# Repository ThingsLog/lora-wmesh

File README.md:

# W-Mesh — reference implementation (Stage 1)

W-Mesh exists to solve one concrete problem: **covering Livingston Island
(Antarctica) with a sensor network without deploying gateway infrastructure
across it**. The Bulgarian Antarctic base runs a duty-cycled LoRaWAN network
— everything sleeps except a ~15-minute daily window — but LoRaWAN is
single-hop, and every additional gateway site (battery, solar, mast) is
infrastructure that must survive the polar winter unattended. Many target
sites (glaciers, ridges, neighbouring bays) can be visited only briefly,
some only by drone.

W-Mesh extends the same windowed, buffered telemetry system with multi-hop
store-and-forward instead: battery relays on ridge lines carry the traffic
of whole valleys and glaciers back to the single existing gateway. Cascade
phases ordered by hop depth, loop freedom by a gradient rule, CAD-gated
listening, and years of battery life on primary cells — coverage grows,
infrastructure does not.

> The underlying windowed deployment this builds on is described in:
> N. Milovanov, B. Tzankov and P. Sapundzhiev, *"Deployment of a low-power
> LoRa LPWAN sensor network for environmental monitoring in Antarctica,"*
> Proc. CompSysTech '26 (Best Paper Award).

Livingston Island is the first deployment, not the limit. The protocol can
be used in **any LoRa/LoRaWAN network whose reach has to grow but where
extra gateways cannot be added, or are not practical to add** — assets one
ridge beyond the last covered valley in water-utility telemetry, remote
farmland, mountain instrumentation, island chains. The mesh layer is
payload-agnostic (relays forward the LoRaWAN frame byte-for-byte and never
read it), so it carries any application format; a device only has to adopt
the windowed discipline: buffer, one slot per day, a fixed channel, the
CAD-length preamble.

## The protocol in short

**The premise.** The whole network — gateway, satellite backhaul, every
node — is asleep except for one scheduled window per day (Livingston:
~15 minutes, anchored at the gateway's Class B beacon around 12:05 UTC).
Nodes buffer a full day of readings and deliver them in that window.
LoRaWAN alone is single-hop; W-Mesh adds store-and-forward on top of it
without touching the LoRaWAN frame.

**The cascade.** The window opens with a short beacon **pre-roll**: the
gateway emits the standard Class B beacon, and relays re-broadcast it
outward tier by tier (in per-relay sub-slots), so every node re-anchors
its clock for the day. Then the uplink **phases** run in order of
DECREASING depth: the deepest tier transmits first while its parents
listen (CAD-gated, ~700× cheaper than continuous RX); each relay then
transmits its own data plus everything it stored, one tier closer to the
gateway per phase. Within a phase every node owns a provisioned time
slot; within the island every tier-1 subtree owns one fixed channel.
Loop freedom needs no timers: a node forwards only frames arriving from
STRICTLY GREATER depth (the gradient rule), so the forwarding graph is a
DAG by construction. One window, one sequence:

**The nodes.** One binary, three provisioned profiles:

| Profile | Measures | Listens | GNSS | Radio budget |
|---|---|---|---|---|
| **leaf** | environment (T/RH) + battery | beacon only | none | ~0.03 mAh/day |
| **relay** | same + forwards its subtree | beacon + CAD phase | optional backup clock (`gnssbk`) | up to ~0.6 mAh/day |
| **stake** | its own GNSS position + battery | beacon only | yes — position IS the payload | ~5 mAh/day (GNSS dominated) |

A stake is technically a leaf (no children); it is a separate profile only
because its payload is the daily averaged GNSS position — the glacier
application. Every profile carries the battery (mV) as its last port.

**The mesh header — where it goes in and where it comes out.** Three
bytes — origin id, sequence, depth|TTL — **prepended to, never written
into, the LoRaWAN frame**:

- **Inserted** by the originating node at transmission; **rewritten** by
  every relay on forward (own depth stamped, TTL decremented). The
  LoRaWAN PHYPayload behind it — ciphertext, frame counter, MIC — is
  forwarded byte-for-byte: relays hold no session keys and need none.
- **Stripped** at tier 1, before the final hop: a tier-1 node knows it is
  the last hop purely from its provisioned depth (d=1 = "my parent is the
  gateway") — no discovery, no flag inside the frame. And there is no MIC
  to restore: it was never modified, so what reaches the gateway is
  byte-identical to what the origin signed, and a standard LoRaWAN
  gateway + network server parse and verify it natively.

Duplicates from multi-parent reception collapse at the next tier via an
(origin, sequence) cache — and at the server via its native multi-gateway
(DevAddr, FCnt) deduplication, to which a W-Mesh relay just looks like
one more gateway reporting a few seconds late.

## Beyond our own devices: the v2 open relay

Stage 1 serves leaves running W-Mesh firmware. The relay service itself,
however, carries opaque LoRaWAN frames (the MIC is never touched), so it can
be opened to plain LoRaWAN devices. [docs/protocol-v2-open-relay.md](docs/protocol-v2-open-relay.md)
specifies how:

- **Adopted mode** — any standard device pinned to the subtree channel and SF,
  sending unconfirmed ABP uplinks on a schedule inside the window; our own
  production loggers qualify with configuration only, no firmware change
- **Negotiated mode** — a TS011-style knock on a well-known control channel;
  the relay answers with an appointment (channel, slot, SF), which doubles as
  over-the-air enrolment
- **CAD gate on every forward** — listen-before-talk ahead of each relay
  transmission, with a path toward ETSI polite spectrum access

The v2 spec also maps W-Mesh onto the LoRaWAN TS011 Relay: TS011 standardises
the device-facing single hop, W-Mesh adds the multi-hop transport that TS011
explicitly leaves out.

## Limitations and technical constraints

W-Mesh buys its energy profile with real sacrifices. They are deliberate,
and anyone planning a deployment should read them before the map.

**What the design gives up on purpose:**

- **Latency.** Data moves once per window. W-Mesh is a telemetry
  architecture, structurally incapable of alarming: an event waits up to a
  day, or two after a missed window. If you need alarms, you need a
  different network (or a cellular/satellite side channel).
- **No self-healing.** Topology is static by design — provisioned, not
  discovered. A dead relay silences its whole subtree until someone visits;
  the only insurance is dual parenting (a critical node placed in earshot
  of two relays), which costs one duplicate frame per window.
- **Uplink only.** The cascade carries nothing outward: a deployed network
  cannot be re-provisioned or commanded remotely. The only downlink-ish
  element is the broadcast beacon, which carries time and nothing else.
- **No per-hop acknowledgements.** Delivery probability falls as p^d with
  hop count, and because the cascade is uplink-only, an origin never learns
  that a copy died mid-path. The remedy is redundancy by design: the
  multi-packet backlog extension carries a sliding window of the last K
  days, so a single mid-path loss is repaired a day late, not never.
- **Energy asymmetry.** A fully loaded relay spends ~20x a leaf's radio
  charge. Still shelf-life-limited on a D cell, but relays are the nodes
  whose batteries set the maintenance calendar.
- **Schedule brittleness.** Phases and slots are sized statically at
  enrolment. The whole edifice rests on time discipline: a node that loses
  the beacon free-runs on a widened guard and, past a configured number of
  days, stays silent rather than trample its neighbours' slots (stakes are
  exempt — their daily GNSS session is absolute time; relays can carry a
  gated GNSS backup clock, `--gnssbk 1`).

**Hard numeric constraints (EU868, SF8 reference):**

| Constraint | Value | Where it comes from |
|---|---|---|
| Fan-in per tier-1 relay | 14 descendants | 1% duty cycle: 36 s TX/hour at ~0.6 s/frame |
| Fan-in per deeper relay | 10 descendants | same budget, CAD-length preamble (~0.8 s/frame) |
| Whitelist capacity | 14 ids | 128 B config image |
| Max depth | 15 tiers | 4-bit depth/TTL fields (practically: p^d ends it earlier) |
| Frame size | one frame ≤ MTU | no fragmentation — 222 B at SF7/8, 51 B at SF10+ |
| Frequency | 1 fixed channel per node (end nodes are single-channel devices) | no hopping — a subtree shares its relay's channel; the relay has a single demodulator; only the gateway hears all 8 |
| Backlog recovery at full fan-in | paced over several windows | 3 days x 14 descendants > the 36 s/h duty budget |
| Clock | temperature-compensated RTC required | an uncompensated 32 kHz crystal loses ~9 s/day at -30 C |
| Beacon | gateway must transmit the Class B beacon | nodes are Class A; only the beacon frame is borrowed |

Status: a design with an analytical model and a working protocol core —
not yet a field-validated system. The numbers above assume an
interference-free window and datasheet CAD behaviour; field validation is
the purpose of the first deployment season.

## Layout

```
core/                 portable protocol core — no vendor, no RTOS, no Arduino
  wmesh_core.h        mesh header, gradient rule, dedup cache, forward queue,
                      cascade phase arithmetic
  wmesh_beacon.h      Class B beacon time discipline: parse/re-stamp + CRC16,
                      pre-roll cascade, missed-beacon guard widening
  wmesh_config.h      provisioning block: 128 B flash image (CRC-guarded),
                      defaults, validation — windowUtcSec is the anchor
  wmesh_console.h     boot console parser (pure, host-tested): show/set/save
  gnss.h              STAKE averaging session: NMEA GGA parse (integer-only),
                      quality filter, streaming mean, position port words
  openlora.h          Open LoRa v5 payloads per the published LPMDL-110X
                      document: analog/pulse readings (FPort 11, differential,
                      pulse final counter 32-bit), battery (FPort 13, 3 B)
  wmesh_port.h        the ONLY hardware surface the core needs (radio/RTC/GNSS)
  wmesh_node.h        node state machine: SLEEP -> beacon RX -> listen(CAD)
                      -> TX (own slot) -> SLEEP; LEAF/RELAY/STAKE profiles
                      (diagrams: docs/wmesh-statemachine.png — states per
                      role; docs/wmesh-seq.png — one window as a sequence)
test/
  host_test.cpp       unit tests for the core — run on your laptop, no hardware
  node_sim_test.cpp   whole-node simulation: a scripted radio + clock drives
                      full windows through wmesh_node.h (beacon acquisition
                      and re-anchor, relay re-stamp/forward/dedup/whitelist,
                      freerun-then-silence) — still no hardware
firmware/stm32wl/
  src/main.cpp        entry point; implementing core/wmesh_port.h over the
                      CubeMX-generated CubeWL drivers is the bench task
firmware/xiao-nrf52840/
  bench node: XIAO nRF52840 + Wio-SX1262 kit, RadioLib port of wmesh_port.h,
  bare-leaf profile (no GNSS, no HDC3020 — battery telemetry only);
  `pio run -t upload`, then tools/hiltest.py smoke-tests the boot console
```

## Target hardware

**Primary target: STM32WLE5 (LoRa-E5 / Wio-E5 class).** MCU and SX126x-class
radio share one die (internal SUBGHZ SPI), STOP2 sleep is ~1 uA with the RTC
running, and the same silicon is the production path for integrating W-Mesh
into the LPMDL logger family. 
Generate the board project with STM32CubeMX
(SUBGHZ + RTC + LPUART for GNSS), then implement `core/wmesh_port.h` over the
CubeWL radio driver (`SUBGRF_*`); the portable core needs no changes.

**Bench target: Seeed XIAO nRF52840 + Wio-SX1262 kit**
(`firmware/xiao-nrf52840/`). The same portable core over RadioLib and the
Arduino BSP — used to bring the mesh logic up on real SX1262 radios before
the STM32WL port lands. Its clock is millis-derived and its sleep is a
FreeRTOS delay loop, so its power posture is bench-grade by design; the
deployment-grade STOP2/RTC discipline belongs to the STM32WL target.

## Deployment topology — Livingston Island

The initial application W-Mesh is designed for: extending the Bulgarian
Antarctic base's windowed LoRaWAN network across the island without new
gateways or solar/battery infrastructure.

```
GW1 + GW2 (BAI base, root redundancy — one collision domain)
├── R1  ridge above the base ── env leaves + Johnsons/Hurd stake clusters
├── R2  Pliska/Bowles ridge
│   └── R4  Kaliakra ridge ──── Kaliakra stake cluster
│        ├── R5  Huron ridge ── Huron stake cluster
│        └── R6  Tangra N slope
├── R3  False Bay ridge ─────── False Bay env nodes
└── R7  west ridge
     └── R8  Byers approach ─── Byers env/stake cluster
```

| Tier | Nodes | Role |
|---|---|---|
| 0 | GW1 + GW2 at the BAI base | beacon source + LoRaWAN uplink; two co-located gateways add redundancy, not capacity |
| 1 | R1, R2, R3 (+R7) | ridge relays in direct reach of the base; also ridge weather stations |
| 2 | R4–R8 | second-hop relays towards the outer glaciers |
| 2–3 | ~30 env leaves + ~60 GNSS stakes | HDC3020 telemetry + glacier kinematics |

Planned fleet load: ~102 nodes ≈ 6.7% of the daily 15-minute window (see
the sizing analysis). A schematic plan,
not a survey product — final positions come from the Stage-1 GNSS+RSSI
site survey.

## Run the core tests (no hardware)

```
c++ -std=c++17 -Wall -Wextra -I core test/host_test.cpp -o wmesh_test
./wmesh_test        # -> ALL W-MESH CORE TESTS PASSED
c++ -std=c++17 -Wall -Wextra -I core test/node_sim_test.cpp -o wmesh_sim
./wmesh_sim         # -> ALL W-MESH NODE SIMULATION TESTS PASSED
```

The tests pin the protocol invariants: strict-gradient acceptance (loop
freedom), TTL exhaustion, duplicate suppression, header re-stamping on
forward, the fan-in-bounded queue (56 = 14 descendants x 4 ports), cascade
phase arithmetic, the OpenLoRa differential round-trip at the
197-byte reference buffer, and the beacon path: CRC16 check vector, beacon
parse/corrupt/re-stamp round-trip (GwSpecific verbatim), the outward pre-roll
ordering, and missed-beacon guard widening. The provisioning layer is tested
end to end: config pack/unpack round-trip with CRC corruption, validation of
broken provisioning, and the full console dialogue including rejected input.

The simulation suite goes one level up: the mock port scripts a radio and a
window clock, and entire windows run through the real state machine
(`core/wmesh_node.h`) — blind-boot beacon acquisition and clock re-anchor,
the leaf's battery frame landing in its provisioned slot, relay beacon
re-stamp (+hop delta, GwSpecific verbatim), store-and-forward with dedup /
whitelist / gradient rejects and last-hop prefix stripping, and the
missed-beacon policy (freerun for `maxFreerunDays`, silence after, revival
on the next caught beacon). On hardware, `tools/hiltest.py` smoke-tests a
real node's boot console over USB serial (command round-trips, validation
rejects, flash save, optional persistence-across-reset check).

## Time discipline: the beacon cascade (no GNSS on relays and leaves)

Phase boundaries rest on clock alignment, and LoRaWAN already ships the
primitive: the **Class B beacon** — 17 bytes at SF9 on 869.525 MHz, carrying
GPS-epoch time, deliberately unencrypted and MIC-free, i.e. legal to
re-broadcast *and* to re-stamp. The window opens with a short **pre-roll**
that cascades the beacon *outward* (uplink phases run deepest-first, so the
deepest tier needs time first):

```
t = 0                  gateway emits the beacon
t = 1 x PREROLL_SLOT   tier-1 relays re-broadcast, time field re-stamped
t = 2 x PREROLL_SLOT   tier-2 relays re-broadcast ...
t = H x PREROLL_SLOT   uplink phases begin (deepest tier transmits first)
```

Nodes count their slots **from beacon reception**, so drift only has to hold
across the window itself (100 ppm x 900 s = 90 ms) — an uncompensated cold
crystal is fine *within* the window, and the wake-up listen (±1 s of RX at
4.6 mA ≈ 0.003 mAh/day) is two orders of magnitude cheaper than a daily GNSS
time fix. **GNSS therefore remains only on the STAKE profile**, where position
*is* the payload and time discipline comes free with the averaging session.
A node that misses the beacon free-runs on its last calibration with a guard
widened per silent day (`widenedGuard`), and past `MAX_FREERUN_DAYS` stays
silent rather than transmit into foreign slots.

## Provisioning: the enrolment console

Everything about **when a node wakes** lives in `wmesh::Config` — a CRC-guarded
128-byte flash page edited over the boot console. Connect USB-UART to LPUART1,
reset, press any key within 3 s:

```
W-Mesh enrolment console — 'help' for commands
> show
> set profile relay
> set depth 1
> set phases 300,600          # deepest first; phase count defines H
> set slot 3                  # private slot inside own TX phase
> set whitelist 31,32,33      # designated children (relay only; - = promiscuous)
> set window 12:05            # THE anchor — see below
> set time 1785060000         # UTC epoch -> RTC; do this LAST, before sealing
> save
OK saved
> boot
```

**The window anchor is the BEACON time, not the power-on time.** On Livingston
the infrastructure timer fires at 12:00 UTC (15:00 Bulgarian summer time), the
gateway + Starlink need ~4 min to boot, and Class B beacons ride a 128 s
GPS-aligned grid — so the first beacon lands somewhere around 12:04–12:06 and,
because 86400 % 128 == 0, **repeats at exactly the same second every day**.
Observe it once, then `set window` to that time on every node.

Two mechanisms make this forgiving:

- **Acquisition mode** (`set acq`, default 360 s): on first boot — or after a
  missed day — the node listens long enough to cover the boot jitter plus one
  full 128 s grid period. After the first caught beacon it drops to the tight
  ±guard listen (~0.003 mAh/day).
- **Blind first wake**: a freshly deployed node has never heard a beacon; its
  first wake-up runs purely on the RTC set by `set time` at enrolment plus
  `windowUtcSec`. That is why `set time` comes last, right before sealing.

Validation runs at `save` and refuses inconsistent provisioning (depth > H,
slot overflowing the own phase, whitelist on a non-relay, >14 children, ...).

The old compile-time constants remain only as `configDefaults()` fallback for
a blank or corrupt flash page.

## The network planner

Hand-assigning slots, channels, beacon sub-slots and whitelists across a
fleet is exactly the bookkeeping that produces field bugs — a whitelist
missing one grandchild silently drops that node's data at the relay.
[`tools/plan.py`](tools/plan.py) does all of it from one JSON file:
**you describe the topology and the goals, it produces the configuration
of every node.**

You write only what a human actually knows (see
[`examples/livingston.json`](examples/livingston.json)):

```json
{
  "window": "12:05",
  "preroll_slot": 5,
  "slot_margin": 2.0,
  "phase_margin": 1.5,
  "channels": [868100000, 868300000, 868500000],
  "nodes": [
    {"id": 21, "name": "R1", "profile": "relay", "parent": 0, "gnssbk": 1},
    {"id": 41, "name": "E1", "profile": "leaf",  "parent": 21},
    {"id": 22, "name": "R4", "profile": "relay", "parent": 23},
    {"id": 51, "name": "S1", "profile": "stake", "parent": 22, "ports": 2}
  ]
}
```

The planner derives the rest: **depth** from the parent chain; the
**channel** (one per tier-1 subtree, inherited downward); the **whitelist**
as ALL descendants of a relay (the firmware filters on the origin id, so a
relay must admit its whole subtree); **beacon sub-slots** per tier;
**slot durations** sized to the heaviest node of each tier (own +
forwarded airtime, extended-preamble aware); and the **phase durations**
from the load times the margin — everything rounded upward on purpose, so
a drifted clock or a late frame lands in slack, not on a neighbour.

It then validates what no node can check about itself — fan-in caps
(14 at tier 1, 10 deeper), whitelist capacity, the 36 s/h duty budget,
slot-fits-phase, parent loops — and emits the deliverables:

```
$ python3 tools/plan.py examples/livingston.json       -o examples/livingston-enroll.sh -t examples/livingston-timeline.png
network: 16 nodes, depth H=3, phases (deepest first) = [42, 162, 99], pre-roll 3x5s
window load: 318s of the 900s window (35%)
  tier 1: 3 nodes, slotdur 22s, channels [868100000, 868300000, 868500000]
  tier 2: 6 nodes, slotdur 18s, channels [868100000, 868300000, 868500000]
  tier 3: 7 nodes, slotdur 4s, channels [868300000, 868500000]
plan OK
enroll script written to examples/livingston-enroll.sh
timeline written to examples/livingston-timeline.png
```

The [enroll script](examples/livingston-enroll.sh) is one ready
`tools/enroll.py` line per node (replace PORT, run, reset the node), and
the **window timeline** shows how every node uses its slots — beacons
(red), listening (hatched), allocated slot (light) and actual airtime
(solid), coloured by channel:

**Scripted enrolment** ([`tools/enroll.py`](tools/enroll.py), needs pyserial):
drives the whole dialogue and sends `set time` with the current UTC second
automatically, LAST — so the RTC error at sealing is bounded by serial latency,
not typing speed. One relay, one line:

```
python3 tools/enroll.py /dev/tty.usbserial-XXX \
    --id 21 --profile relay --depth 1 --phases 300,600 \
    --slot 3 --whitelist 31,32,33 --window 12:05 --boot
```

It aborts on the first `ERR` (nothing is saved), prints `show` before saving,
and `--show` alone just inspects a sealed-config node. Reset the node right
after starting the script — it presses the "any key" for you.

## For testers: building and accepting relay nodes

The per-board production flow — flash over SWD with a clone ST-Link,
service-console provisioning, bench validation, overnight soak, sleep-current
acceptance — is a single runbook: [docs/tester-guide.md](docs/tester-guide.md).
The proven STM32WL flash recipe is scripted in
[tools/flash-stm32wl.tcl](tools/flash-stm32wl.tcl).

## Flash & test

Step-by-step bring-up — unlocking the factory LoRa-E5 (RDP), CubeMX project
generation, flashing over SWD, the two-module bench test, air monitoring,
PPK2 power validation against the energy model, GNSS time-discipline
check and the 24-hour field dry-run — lives in
[`docs/flash-and-test.md`](docs/flash-and-test.md).

## Status

Protocol core: implemented and host-tested. STM32WL port layer: interface
frozen, CubeWL glue pending (Stage 1 bench). 

License: MIT.

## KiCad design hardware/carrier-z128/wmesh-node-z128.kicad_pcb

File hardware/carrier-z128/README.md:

# W-Mesh Node carrier (Z128) — hardware

Single-board carrier for a W-Mesh tier-1 relay / stake node, sized for a **Kradex Z128**
enclosure (105 × 70 × 40 mm, PC/ABS). It hosts the bare **LoRa-E5-HF** module and the
**Seeed L76K GNSS for XIAO** module soldered as modules, plus the GPS power gate,
decoupling, battery/VIN interface and programming/console headers.

All mechanical/electrical data below is from authoritative sources (Seeed LoRa-E5 datasheet
V1.0 Table 1, Seeed OPL KiCad footprints, Kradex Z128 drawing). **One item is provisional —
the mounting-hole positions — see "Enclosure".**

### Status (validated with KiCad 10.0.7 CLI)
- Board **opens and renders** cleanly (`render-top.png`).
- DRC: **no fab-critical errors** (no shorts / clearance / copper / drill). Remaining items are
  the expected **ratsnest** (board is placed but **NOT routed** — route it in KiCad) plus
  cosmetic silk/lib warnings that KiCad clips at plot.
- **Remaining step = routing.** In KiCad: `Route → Router`, or Freerouting
  (`File → Export → Specctra DSN` → freerouting → import `.ses`). GND is a pour on both layers,
  so route the signal/power nets; press `B` to fill zones. Then plot Gerbers.

## Modules hosted

| Ref | Module | Footprint (authoritative) | Source |
|-----|--------|---------------------------|--------|
| U1  | LoRa-E5-HF (STM32WLE5JC + SX126x) | `LoRa-E5.kicad_mod` (SMD-28, 12×12 mm, 1.25 mm pitch) | Seeed OPL lib |
| U2  | L76K GNSS for XIAO (Quectel L76K) | `XIAO-Add-On.kicad_mod` (2×7 THT, 2.54 mm, rows 17.78 mm) | Seeed OPL lib |

Both footprints are bundled in `footprints/wmesh.pretty/`.

## Net / connection table (the actual design)

LoRa-E5 pad numbers are from the Seeed datasheet (Table 1). L76K pads use XIAO silk names.

| Net | LoRa-E5 (U1) | L76K (U2) | Other |
|-----|--------------|-----------|-------|
| **VDD** (always-on rail) | pad1 VCC | — | Q1 source, R1, R2, U3.OUT (via SB1), C3/C4, J3.3V3, J4.3V3 |
| **GPS_VCC** (gated) | — | 3V3 pad | Q1 drain, C1+C2, U2 STBY(D0) tie |
| **PB4_GATE** | pad7 PB4 | — | Q1 gate, R1→VDD |
| **MCU_LPUART_RX** | pad13 PC0 | D7 (GPS TX) | — |
| **MCU_LPUART_TX** | pad12 PC1 | D6 (GPS RX) | — |
| **UART_TX** (console) | pad10 PB6 | — | J3.TX |
| **UART_RX** (console) | pad9 PB7 | — | J3.RX |
| **SWDIO** | pad3 PA13 | — | J4.SWDIO |
| **SWCLK** | pad4 PA14 | — | J4.SWCLK |
| **NRST** | pad17 RST | — | J4.NRST |
| **BOOT** | pad24 PB13 | — | R2→VDD, J5.1 |
| **RF** | pad15 RFIO | — | J6 u.FL signal |
| **GND** | pads 2,14,16,22 | GND pad | everything, J6 shield |

### GPS gate logic
`PB4 = LOW → Q1 (P-FET) ON → GPS powered`. R1 (100k) pulls the gate to VDD so GPS is **OFF
by default** (reset / Hi-Z). **Firmware: set `GPS_GATE_ON = LOW`** in `wmesh_port_stm32wl.cpp`
(currently HIGH for the shield's STANDBY style). GPS STANDBY (D0) is tied to GPS_VCC = runs
whenever powered. Warm vs cold start depends on the L76K module's onboard RTC backup; either
way the early-exit GNSS firmware minimises on-time.

## Power — READ THIS

VBAT connects **directly to VCC, no regulator** (1.8–3.6 V window of STM32WL/L76K).

- **Field (J1):** 3.6 V **LiSOCl₂** EVE ER26500 (C) **in parallel with EVE HLC1520** hybrid
  cap (off-board, wired to J1). The HLC buffers LoRa-TX / GPS-inrush pulses. SB1 = VBAT-direct.
- **Bench (J2 + U3):** a plain **18650 is 4.2 V > 3.6 V abs-max — NEVER on J1.** Feed it (or
  USB 5 V) to **J2**, through the **HT7333 LDO (U3)** → 3.3 V, and set **SB1 = LDO-out**.
- **SB1 selects exactly one source. Never bridge both.**

## Enclosure (Kradex Z128)

- External 105 × 70 × 40 mm; internal height ≈ 32.9 mm (room for a C-cell / 18650 laid flat).
- **PCB outline: 62.65 × 94.45 mm, corner radius 3 mm** (fits the base cavity + side guides).
- **Mounting holes H1–H4: Ø2.8** for the box's Ø2.5 self-tapping posts (posts are Ø6 OD —
  Ø6 copper keep-out around each). Pattern used: columns 52.65 mm apart, rows 71 mm apart
  (2 of the 6 posts top+bottom), centred.
  **⚠ PROVISIONAL** — read off the Kradex drawing, not yet confirmed to the physical box.
  Verify against your Z128 (or the Kradex STEP) and nudge H1–H4 in KiCad before ordering.
- u.FL (J6) + both antennas exit one end wall; drill the Z128 wall for pigtails/SMA.

## Files

- `footprints/wmesh.pretty/` — the two module footprints (authoritative).
- `BOM.csv` — bill of materials with JLC/LCSC codes (verify codes in JLC parts search).
- `schematic.svg` — human-readable schematic for review.
- `wmesh-node-z128.kicad_pro` / `.kicad_pcb` — KiCad 8 board (open, finish routing, DRC, plot).

## Ordering from JLCPCB

1. Open `wmesh-node-z128.kicad_pcb` in **KiCad 8**. Run **DRC**; finish any ratsnest routing.
2. **File → Plot**: Gerbers (F.Cu, B.Cu, F/B.SilkS, F/B.Mask, F/B.Paste, Edge.Cuts),
   Protel extensions off, then **Generate Drill Files** (Excellon, PTH+NPTH merged).
3. Zip the Gerber/drill folder → upload to JLCPCB. Settings: **2-layer, 1.6 mm, HASL
   (or ENIG), 1 oz Cu**. Z128 PCB is 62.65 × 94.45 mm.
4. SMT assembly (optional): Q1, R1/R2, C1–C6, J1/J2, J6, U3. **U1 (LoRa-E5) and U2 (L76K)
   are hand-soldered modules** — exclude from SMT. Export BOM + CPL (pick-and-place) from KiCad.
5. Hand-solder U1, U2, headers J3/J4/J5. Flash U1 via J4 (SWD). Set `GPS_GATE_ON = LOW`.

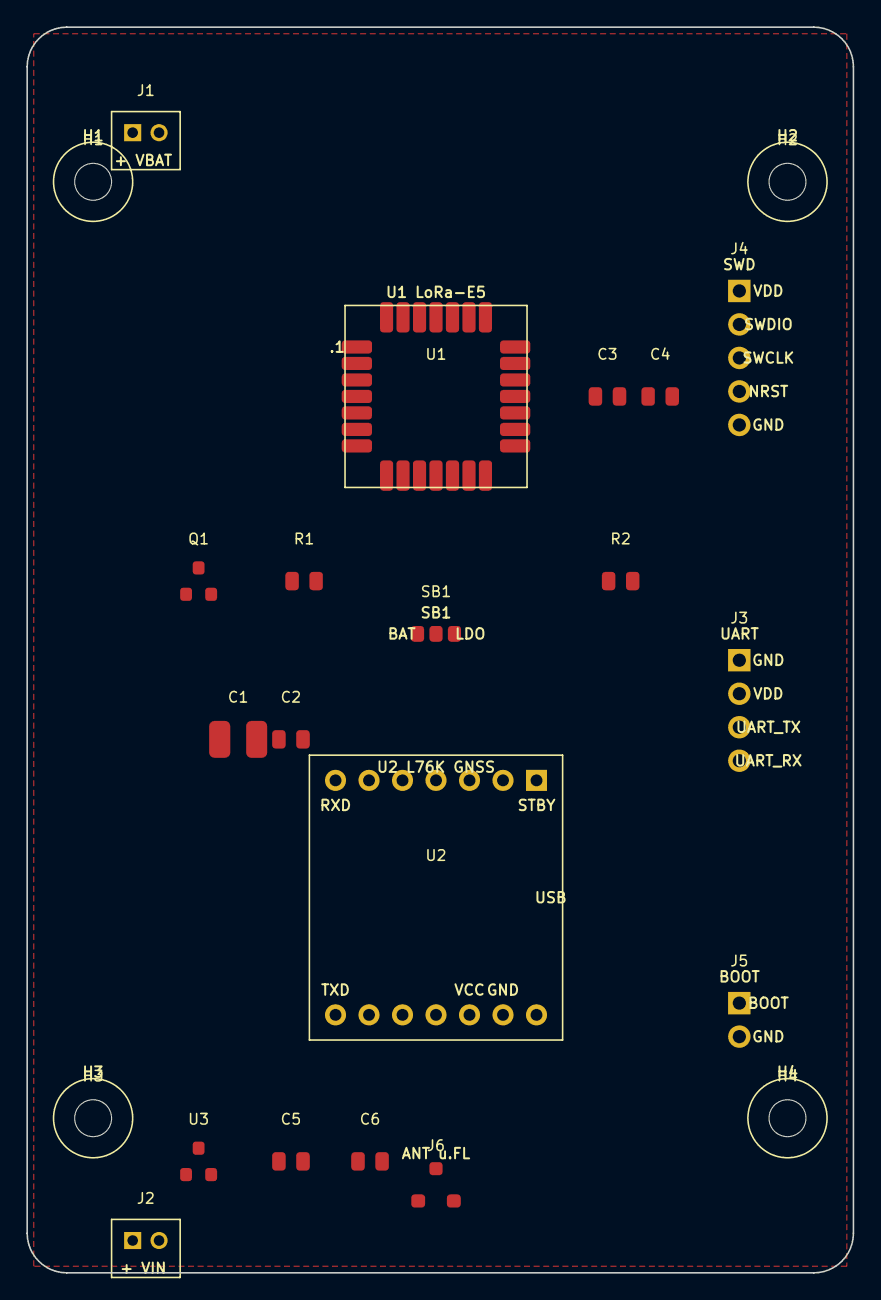
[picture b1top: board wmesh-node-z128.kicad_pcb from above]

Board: 2 copper layers, 62.6 x 94.5 mm, 23 parts (0 on the bottom side), 16 nets, no tracks yet.

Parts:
C1: 100uF; C_1210
C2, C4: 100nF; C_0805
C3: 10uF; C_0805
C5, C6: 1uF; C_0805
H1, H2, H3, H4: Mnt; MountingHole_2.8
J1: BATT; JST_PH_2
J2: VIN; JST_PH_2
J3: UART; PinHeader_1x4
J4: SWD; PinHeader_1x5
J5: BOOT; PinHeader_1x2
J6: u.FL; uFL_SMD
Q1: IRLML6402; SOT-23
R1, R2: 100k; C_0805
SB1: SRC; SolderJumper_3
U1: LoRa-E5-HF; LoRa-E5
U2: L76K-GNSS-XIAO; L76K_XIAO
U3: MCP1700-3302; SOT-23

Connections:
BOOT: J5.1, R2.1, U1.24
GND: C1.2, C2.2, C3.2, C4.2, C5.2, C6.2, J1.2, J2.2, J3.1, J4.5, J5.2, J6.2, J6.3, U1.2, U1.14, U1.16, U1.22, U2.9, U3.2
GPS_VCC: C1.1, C2.1, Q1.3, U2.1, U2.10
LPUART_RX: U1.13, U2.14
LPUART_TX: U1.12, U2.7
NRST: J4.4, U1.17
PB4_GATE: Q1.1, R1.1, U1.7
RF: J6.1, U1.15
SWCLK: J4.3, U1.4
SWDIO: J4.2, U1.3
UART_RX: J3.4, U1.9
UART_TX: J3.3, U1.10
VBAT: J1.1, SB1.1
VDD: C3.1, C4.1, J3.2, J4.1, Q1.2, R1.2, R2.2, SB1.2, U1.1
VDD_LDO: C6.1, SB1.3, U3.3
VIN: C5.1, J2.1, U3.1
